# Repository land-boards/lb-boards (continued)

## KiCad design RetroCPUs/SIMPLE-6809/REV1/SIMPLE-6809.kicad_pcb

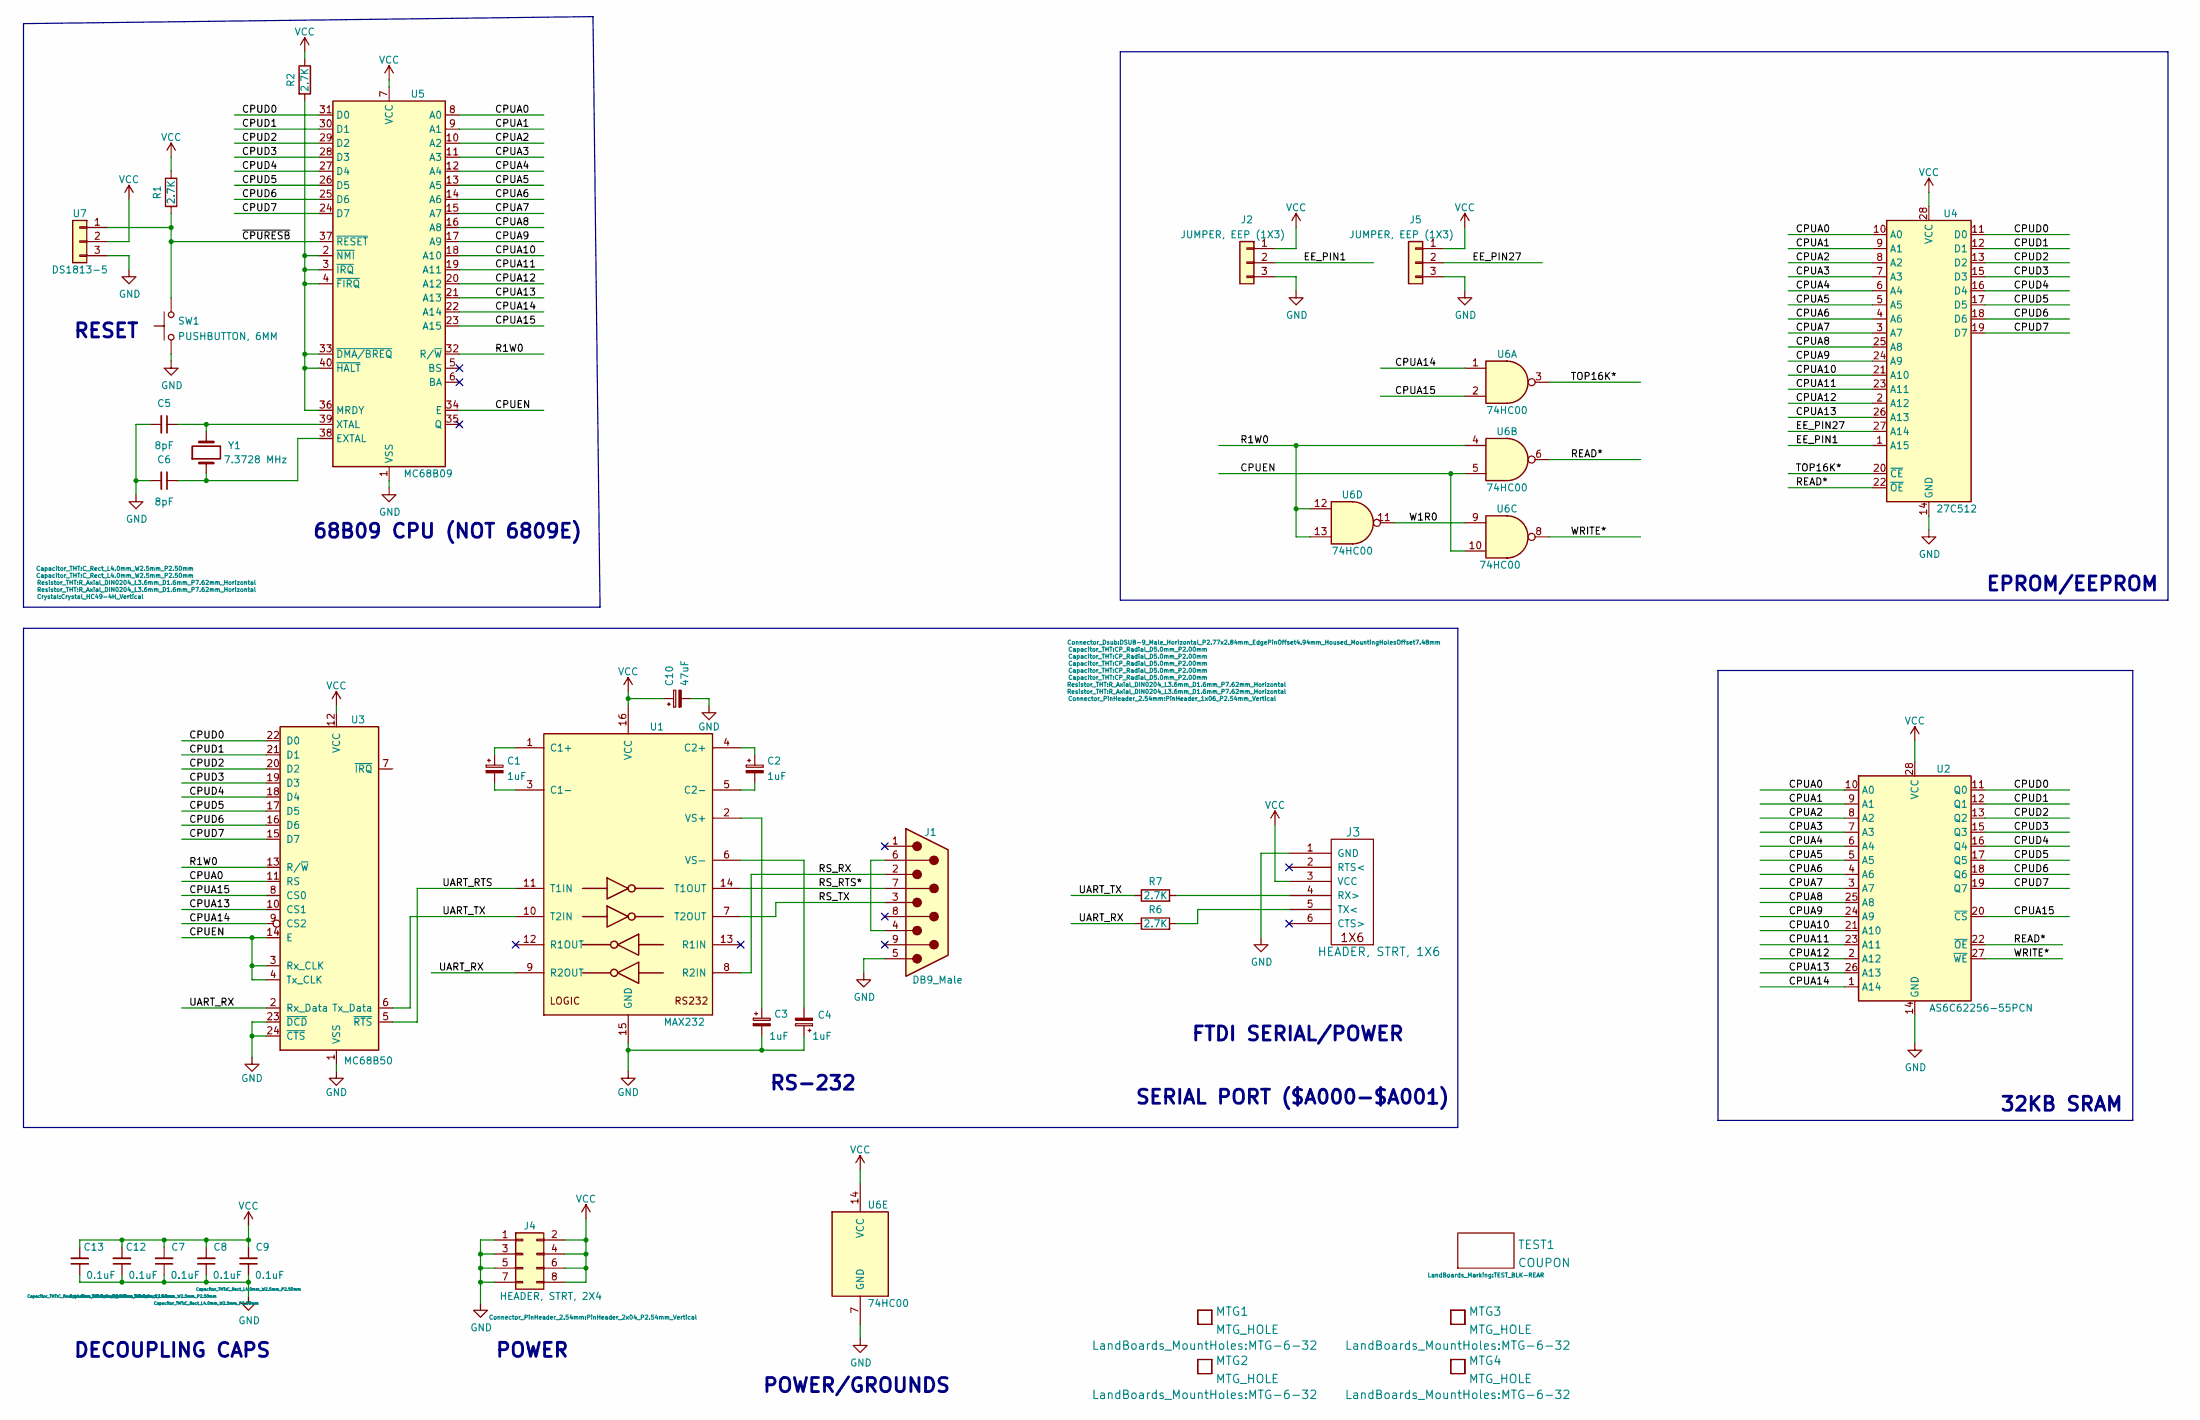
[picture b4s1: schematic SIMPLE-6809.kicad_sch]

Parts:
C1, C2, C3, C4: 1uF; CP_Radial_D5.0mm_P2.00mm
C5, C6: 8pF; C_Rect_L4.0mm_W2.5mm_P2.50mm
C7, C8, C9, C12, C13: 0.1uF; C_Rect_L4.0mm_W2.5mm_P2.50mm
C10: 47uF; CP_Radial_D5.0mm_P2.00mm
J1: DB9_Male; DSUB-9_Male_Horizontal_P2.77x2.84mm_EdgePinOffset4.94mm_Hou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
J2, J5: JUMPER, EEP (1X3); PinHeader_1x03_P2.54mm_Vertical
J3: HEADER, STRT, 1X6; PinHeader_1x06_P2.54mm_Vertical
J4: HEADER, STRT, 2X4; PinHeader_2x04_P2.54mm_Vertical
MTG1, MTG2, MTG3, MTG4: MTG_HOLE; MTG-6-32
R1, R2, R6, R7: 2.7K; R_Axial_DIN0204_L3.6mm_D1.6mm_P7.62mm_Horizontal
SW1: PUSHBUTTON, 6MM; SW_PUSH_6mm_H8.5mm
TEST1: COUPON; TEST_BLK-REAR
U1: MAX232; DIP-16_W7.62mm_LongPads
U2: AS6C62256-55PCN; DIP-28_W15.24mm
U3: MC68B50; DIP-24_W15.24mm
U4: 27C512; DIP-28_W15.24mm
U5: MC68B09; DIP-40_W15.24mm
U6: 74HC00; DIP-14_W7.62mm_LongPads
U7: DS1813-5; TO-92
Y1: 7.3728 MHz; Crystal_HC49-4H_Vertical

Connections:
/CPUA0: U2.10 (A0), U3.11 (RS), U4.10 (A0), U5.8 (A0)
/CPUA1: U2.9 (A1), U4.9 (A1), U5.9 (A1)
/CPUA2: U2.8 (A2), U4.8 (A2), U5.10 (A2)
/CPUA3: U2.7 (A3), U4.7 (A3), U5.11 (A3)
/CPUA4: U2.6 (A4), U4.6 (A4), U5.12 (A4)
/CPUA5: U2.5 (A5), U4.5 (A5), U5.13 (A5)
/CPUA6: U2.4 (A6), U4.4 (A6), U5.14 (A6)
/CPUA7: U2.3 (A7), U4.3 (A7), U5.15 (A7)
/CPUA8: U2.25 (A8), U4.25 (A8), U5.16 (A8)
/CPUA9: U2.24 (A9), U4.24 (A9), U5.17 (A9)
/CPUA10: U2.21 (A10), U4.21 (A10), U5.18 (A10)
/CPUA11: U2.23 (A11), U4.23 (A11), U5.19 (A11)
/CPUA12: U2.2 (A12), U4.2 (A12), U5.20 (A12)
/CPUA13: U2.26 (A13), U3.10 (CS1), U4.26 (A13), U5.21 (A13)
/CPUA14: U2.1 (A14), U3.9 (CS2), U5.22 (A14), U6.1
/CPUA15: U2.20 (~CS), U3.8 (CS0), U5.23 (A15), U6.2
/CPUD0: U2.11 (Q0), U3.22 (D0), U4.11 (D0), U5.31 (D0)
/CPUD1: U2.12 (Q1), U3.21 (D1), U4.12 (D1), U5.30 (D1)
/CPUD2: U2.13 (Q2), U3.20 (D2), U4.13 (D2), U5.29 (D2)
/CPUD3: U2.15 (Q3), U3.19 (D3), U4.15 (D3), U5.28 (D3)
/CPUD4: U2.16 (Q4), U3.18 (D4), U4.16 (D4), U5.27 (D4)
/CPUD5: U2.17 (Q5), U3.17 (D5), U4.17 (D5), U5.26 (D5)
/CPUD6: U2.18 (Q6), U3.16 (D6), U4.18 (D6), U5.25 (D6)
/CPUD7: U2.19 (Q7), U3.15 (D7), U4.19 (D7), U5.24 (D7)
/CPUEN: U3.3 (Rx_CLK), U3.4 (Tx_CLK), U3.14 (E), U5.34 (E), U6.5, U6.10
/EE_PIN1: J2.2, U4.1 (A15)
/EE_PIN27: J5.2, U4.27 (A14)
/R1W0: U3.13 (R/~W), U5.32 (R/~W), U6.4, U6.12, U6.13
/READ*: U2.22 (~OE), U4.22 (~OE), U6.6
/RS_RTS*: J1.7, U1.14 (T1OUT)
/RS_RX: J1.2, U1.8 (R2IN)
/RS_TX: J1.3, U1.7 (T2OUT)
/TOP16K*: U4.20 (~CE), U6.3
/UART_RTS: U1.11 (T1IN), U3.5 (~RTS)
/UART_RX: R6.1, U1.9 (R2OUT), U3.2 (Rx_Data)
/UART_TX: R7.1, U1.10 (T2IN), U3.6 (Tx_Data)
/W1R0: U6.9, U6.11
/WRITE*: U2.27 (~WE), U6.8
/~CPURESB: R1.2, SW1.2, U5.37 (~RESET), U7.1
GND: C3.2, C4.1, C5.2, C6.2, C7.1, C8.1, C9.1, C10.2, C12.1, C13.1, J1.5, J2.3, J3.1 (GND), J4.1, J4.3, J4.5, J4.7, J5.3, SW1.1, U1.15 (GND), U2.14 (GND), U3.1 (VSS), U3.23 (~DCD), U3.24 (~CTS), U4.14 (GND), U5.1 (VSS), U6.7 (GND), U7.3
unnamed: J1.4, J1.6
unnamed: J3.4 (RX>), R7.2
unnamed: J3.5 (TX<), R6.2
unnamed: C1.1, U1.1 (C1+)
unnamed: C1.2, U1.3 (C1-)
unnamed: C2.1, U1.4 (C2+)
unnamed: C2.2, U1.5 (C2-)
unnamed: C3.1, U1.2 (VS+)
unnamed: C4.2, U1.6 (VS-)
unnamed: C6.1, U5.38 (EXTAL), Y1.1
unnamed: R2.2, U5.2 (~NMI), U5.3 (~IRQ), U5.4 (~FIRQ), U5.33 (~DMA/BREQ), U5.36 (MRDY), U5.40 (~HALT)
unnamed: C5.1, U5.39 (XTAL), Y1.2
VCC: C7.2, C8.2, C9.2, C10.1, C12.2, C13.2, J2.1, J3.3 (VCC), J4.2, J4.4, J4.6, J4.8, J5.1, R1.1, R2.1, U1.16 (VCC), U2.28 (VCC), U3.12 (VCC), U4.28 (VCC), U5.7 (VCC), U6.14 (VCC), U7.2

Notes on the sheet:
POWER
RESET
32KB SRAM
DECOUPLING CAPS
FTDI SERIAL/POWER
SERIAL PORT ($A000-$A001)
POWER/GROUNDS
EPROM/EEPROM
68B09 CPU (NOT 6809E)
RS-232

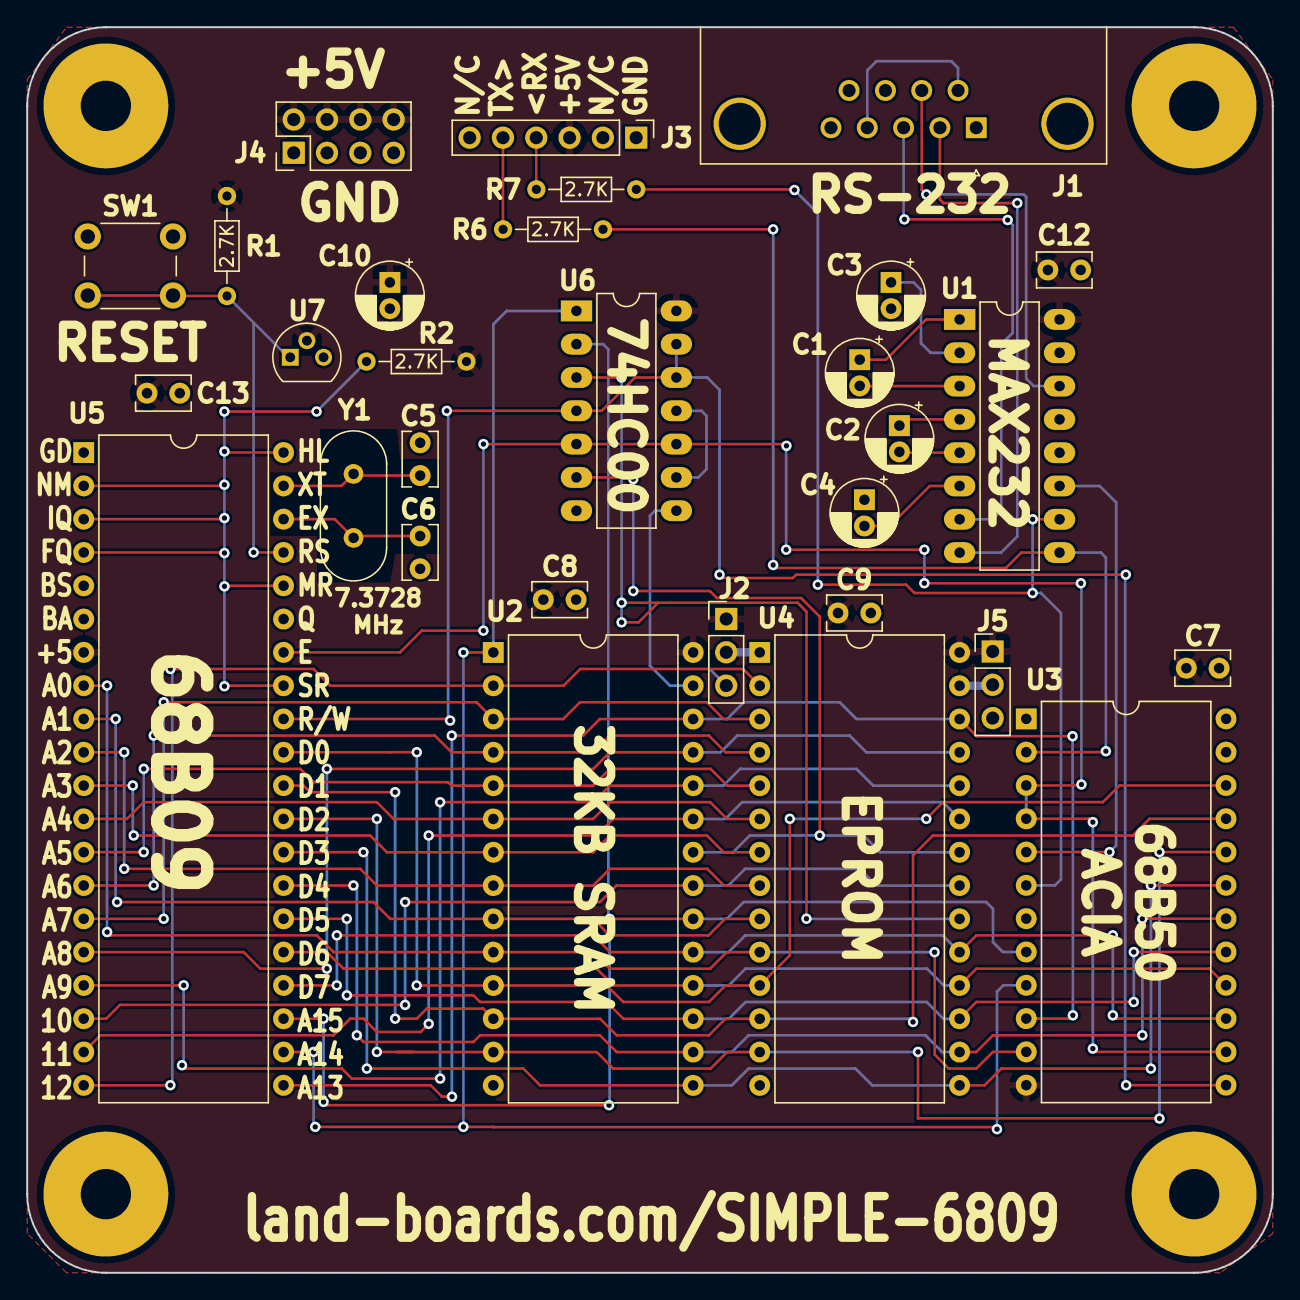
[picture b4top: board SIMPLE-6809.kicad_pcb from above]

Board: 2 copper layers, 95.0 x 95.0 mm, 35 parts (0 on the bottom side), 53 nets.

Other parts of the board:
TEST: COUPON; TEST_BLK-REAR
